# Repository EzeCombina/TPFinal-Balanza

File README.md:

# Balanza 0-30 Kg
## Trabajo práctico final de Electrónica Aplicada II y Teoría de Circuitos II. UTN FR San Francisco
En este repositorio se encuentran subidos todos los archivos relacionados al trabajo práctico de amplificadores operacionales de Electrónica Aplicada II y filtros digitales de Teoría de Circuitos II. Contiene archivos de programación del microcontrolador ATMega328p, archivos de la placa realizada en KiKad, la simulación en Multisim del amplificador de instrumentación y el programa de cálculo del filtro en Octave.
## Autores
- Combina Ezequiel
* Giorgis Guillermo

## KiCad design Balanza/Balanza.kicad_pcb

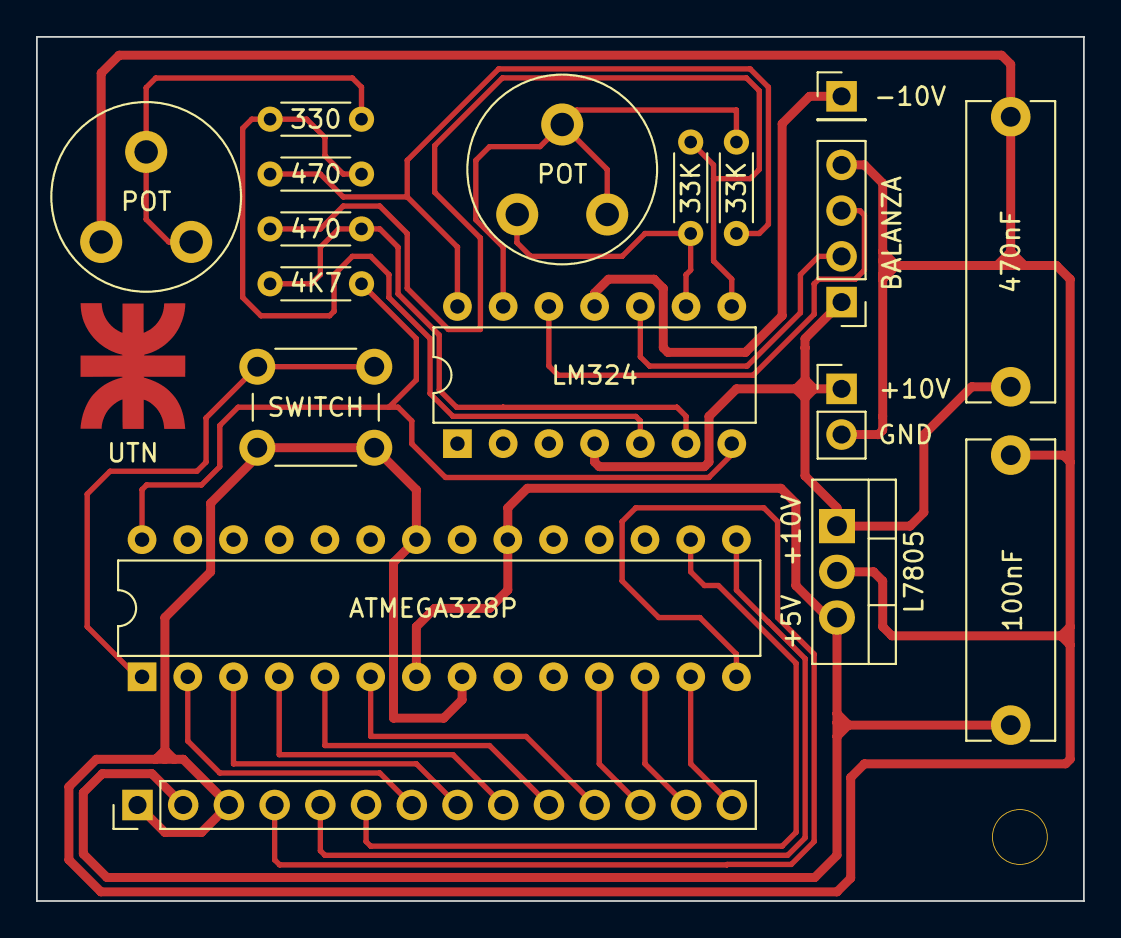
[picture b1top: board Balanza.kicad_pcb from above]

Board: 2 copper layers, 58.2 x 48.0 mm, 18 parts (0 on the bottom side), 26 nets.

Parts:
4K7, 330: 4K7; R_Axial_DIN0204_L3.6mm_D1.6mm_P5.08mm_Horizontal
33K, 33K#2: 33K; R_Axial_DIN0204_L3.6mm_D1.6mm_P5.08mm_Horizontal
100nF: 100nF; C_Rect_L16.5mm_W4.7mm_P15.00mm_MKT
470, 470#2: 470; R_Axial_DIN0204_L3.6mm_D1.6mm_P5.08mm_Horizontal
470nF: 470nF; C_Rect_L16.5mm_W4.7mm_P15.00mm_MKT
+10V: Conn_01x02_Male; PinHeader_1x02_P2.54mm_Vertical
-10V: Conn_01x01_Male; PinHeader_1x01_P2.54mm_Vertical
ATMEGA328P: ATmega328P-P; DIP-28_W7.62mm
BALANZA: Conn_01x04_Male; PinHeader_1x04_P2.54mm_Vertical
J1: Conn_01x14_Male; PinHeader_1x14_P2.54mm_Vertical
L7805: L7805; TO-220-3_Vertical
LM324: LM324; DIP-14_W7.62mm
POT: R_Variable; Potentiometer_Piher_PT-10-V05_Vertical
POT#2: R_Variable; Potentiometer_Piher_PT-10-V05_Vertical
SWITCH: SW_Push_Dual_x2; SW_PUSH_6mm

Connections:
+5V: 100nF.1, ATMEGA328P.7 (VCC), ATMEGA328P.20 (AVCC), J1.2, L7805.3 (OUT)
+10V: 470nF.1, +10V.1, BALANZA.1, L7805.1 (IN), LM324.4 (V+)
/ADC: 4K7.1, ATMEGA328P.28 (PC5), LM324.7
/Data+: BALANZA.3, LM324.12 (+)
/Data-: BALANZA.2, LM324.10 (+)
/PB0 RS: ATMEGA328P.14 (PB0), J1.4
/PB1 RW: ATMEGA328P.15 (PB1), J1.5
/PB2 E: ATMEGA328P.16 (PB2), J1.6
/PD0: ATMEGA328P.2 (PD0), J1.7
/PD1: ATMEGA328P.3 (PD1), J1.8
/PD2: ATMEGA328P.4 (PD2), J1.9
/PD3: ATMEGA328P.5 (PD3), J1.10
/PD4: ATMEGA328P.6 (PD4), J1.11
/PD5: ATMEGA328P.11 (PD5), J1.12
/PD6: ATMEGA328P.12 (PD6), J1.13
/PD7: ATMEGA328P.13 (PD7), J1.14
/RESET: ATMEGA328P.1 (~RESET/PC6), SWITCH.1 (C)
/Vcc_-10V: -10V.1, LM324.11 (V-)
Earth: 100nF.2, 470nF.2, +10V.2, ATMEGA328P.8 (GND), ATMEGA328P.22 (GND), BALANZA.4, J1.1, J1.3, L7805.2 (GND), POT.3, SWITCH.2 (D)
unnamed: 33K.1, LM324.9 (-), POT#2.3
unnamed: 33K.2, 470.2, LM324.8
unnamed: 33K#2.1, 470#2.2, LM324.14
unnamed: 4K7.2, 470.1, LM324.6 (-)
unnamed: 330.2, 470#2.1, LM324.5 (+)
unnamed: 330.1, POT.1, POT.2
unnamed: 33K#2.2, LM324.13 (-), POT#2.1, POT#2.2

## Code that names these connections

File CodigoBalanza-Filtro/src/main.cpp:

#include <Arduino.h>
#include <LiquidCrystal.h>

#define TiempoMuestreoMS 9.09

const char pinRs = 8;         // PB0
const char pinRw = 9;         // PB1
const char pinE = 10;         // PB2
const char pinD4 = 4;         // PD4
const char pinD5 = 5;         // PD5
const char pinD6 = 6;         // PD6
const char pinD7 = 7;         // PD7
const char pinADC = A5;       // PC5

// Logo UTN

byte UTN[8] {

  B10101,
  B01110,
  B00100,
  B11111,
  B00100,
  B01110,
  B10101,
  B00000
  
};

//

//const float CoefEntrada[5] = {0.2194, 0.8778, 1.3167, 0.8778, 0.2194};
//const float CoefSalida[5] = {1, -1.1989, -0.9437, -0.3194, -0.049};

const float CoefEntrada[5] = {0.1237, 0.4949, 0.7423, 0.4949, 0.1237};
const float CoefSalida[5] = {1, -0.3566, -0.5262, -0.07653, -0.02015};

float ArrayEntrada[5] = {0, 0, 0, 0, 0};
float ArraySalida[5] = {0, 0, 0, 0, 0}; 

float Peso = 0.0;
float valorAntiguo = 0.0;

LiquidCrystal lcd(pinRs, pinRw, pinE, pinD4, pinD5, pinD6, pinD7);

unsigned long TiempoMedido = 0;

void calculopeso(float valorADC){

  //if((valorADC < valorAntiguo + 0.5) && (valorADC > valorAntiguo - 0.5))
  //{
  //  valorADC = valorAntiguo;
  //}

  // --- Cálculos para evitar errores en la medición --- Habria que realizar una función de linealización //

  valorADC = valorADC - 9.5;

  if(valorADC <= 0.1){

    Peso = 0.0;

  }else if(valorADC < 30)
  {
    
    Peso = (valorADC + 2) * 30 / 1023;
  
  }else if(valorADC > 100)
  {
    
    Peso = (valorADC + 10) * 30 / 1023;
    
  }else{Peso = (valorADC + 5) * 30 / 1023;}

  //valorAntiguo = valorADC;

  /*
  valorADC = valorADC - 11;
  if(valorADC <= 0.1){

    Peso = 0.0;

  }else{Peso = (valorADC + 5) * 30 / 1024;}
  */

  //float Peso = (valorADC + 1) * 30 / 1024;

  // --- Evitar que parpadee --- //

  if((Peso < valorAntiguo + 0.025) && (Peso > valorAntiguo - 0.025)) 
  {
    Peso = valorAntiguo;
  }

  lcd.setCursor(0,0);
  lcd.print("     ");
  lcd.print(Peso, 2);
  lcd.print(" kg    ");

  valorAntiguo = Peso;

}

void datosEntrada(){
  TiempoMedido = millis();
  ArrayEntrada[0] = float(analogRead(pinADC));
}

void filtro(){
  float sumatoria = CoefEntrada[0]*ArrayEntrada[0];
  for(int i = 1; i < 5; i++){
    sumatoria += CoefEntrada[i] * ArrayEntrada[i] + CoefSalida[i] * ArraySalida[i];
  }
  ArraySalida[0] = sumatoria;
}

void corrimientoArray(){
  for(int i = 4; i > 0; i--){
    ArraySalida[i] = ArraySalida[i-1];
    ArrayEntrada[i] = ArrayEntrada[i-1];
  }
}

void pines(){
  pinMode(pinADC, INPUT);
  pinMode(pinRs, OUTPUT);
  pinMode(pinRw, OUTPUT);
  pinMode(pinE, OUTPUT);
  pinMode(pinD4, OUTPUT);
  pinMode(pinD5, OUTPUT);
  pinMode(pinD6, OUTPUT);
  pinMode(pinD7, OUTPUT);
}

void inicializacionLCD(){
  lcd.begin(16, 2);
  lcd.setCursor(0, 1);
  lcd.print("  UTN FR SFCO");
  lcd.write(byte(0));
}

void setup() {
  pines();
  lcd.createChar(0, UTN);
  //lcd.clear();
  inicializacionLCD();
  TiempoMedido = millis();
  Serial.begin(9600);
}

void loop() {
  if(millis() - TiempoMedido >= TiempoMuestreoMS){
    datosEntrada();
    filtro();
    Serial.println(ArraySalida[0]);
    calculopeso(ArraySalida[0]);
    corrimientoArray(); 
  }
}

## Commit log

2023-11-12 Se vuelven a cargar los archivos por separado
2023-11-12 Codigos
2023-11-12 KiKad
2023-11-12 Cambio
2023-11-12 CódigoBalanza
2023-11-12 Código Octave
2023-11-14 Cambio - Dividido 2
2023-11-14 Modificaciones
2023-11-14 Código Final
2023-11-15 Multisim
2023-11-15 Circuito Final
2023-11-16 Imágenes y Videos
